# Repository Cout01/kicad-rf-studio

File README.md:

# kicad-rf-studio

kicad-rf-studio imports KiCad boards and simulates their RF parts with openEMS. It is free software, licensed under the GNU General Public License v3.0 or later (see `LICENSE`); its copy of CSXCAD's SmoothMeshLines is under the GNU Lesser General Public License v3.0 or later (see `COPYING.LESSER`).

*Em português: [README.pt-BR.md](README.pt-BR.md).*

## Install

kicad-rf-studio runs from a virtual environment of its own, `<venv>` below. pip installs it there with its Python dependencies, Qt among them (about 600 MB on disk); openEMS 0.37 comes apart. Until kicad-rf-studio is on PyPI, `<source>` is the source zip of a release on the project's GitHub page, once the project is published there, or a clone of this repository.

### Windows

In PowerShell, on Windows 10 or 11:

1. Install Python 3.14, 64-bit, for your user: with the Python install manager (`py install 3.14`), which needs no admin rights, or from python.org. The openEMS 0.37 wheels for Windows need Python 3.13 or 3.14.
2. Make the venv at `%LOCALAPPDATA%\kicad-rf-studio\venv` and install kicad-rf-studio into it. `$venv` names it in the commands below; a new PowerShell window needs that first line again.

   ```
   $venv = "$env:LOCALAPPDATA\kicad-rf-studio\venv"
   py -3.14 -m venv $venv
   & "$venv\Scripts\python" -m pip install <source>
   ```

3. Unpack the official Windows package of openEMS 0.37 and give its folder, the one that holds `openEMS.exe` and `python\`, to `setup-openems`. It installs the package's openEMS and CSXCAD wheels into the venv, offline, and records the folder.

   ```
   & "$venv\Scripts\kicad-rf-studio" setup-openems "<openEMS folder>"
   ```

4. Start KiCad once first, so that it makes its version's folder (or name the version with `--kicad 9.0` or `--kicad 10.0`). Install the KiCad button, for KiCad 9.0.7 or later, or 10.x. It writes into each KiCad version's plugins folder and never edits KiCad's settings. Then, in KiCad: Preferences › Plugins › Enable KiCad API, then restart KiCad.

   ```
   & "$venv\Scripts\kicad-rf-studio" install-kicad-plugin
   ```

5. Start the GUI with `& "$venv\Scripts\kicad-rf-studio-gui"`, or from KiCad's PCB editor: select the chain's two end pads, the antenna footprint (or one of its pads) and the radio pin, or a track, arc or via of a signal-integrity line, and press the kicad-rf-studio button. After updating kicad-rf-studio, run `install-kicad-plugin` again: the button's tooltip, which says what it takes, is written there.

### Linux

On Debian 12, Ubuntu 24.04 or Fedora (glibc 2.34 or newer), with the system Python (3.11 or newer):

1. Clone upstream's openEMS-Project at v0.37.0, with its submodules, and install its build dependencies. This is the one step that needs admin rights: the script asks, then installs your distribution's packages with sudo, `python3-venv` among them on Debian and Ubuntu.

   ```
   git clone --recursive --branch v0.37.0 https://github.com/thliebig/openEMS-Project.git
   cd openEMS-Project
   ./scripts/install_deps.sh --install --python
   ```

2. Make the venv at `~/.local/share/kicad-rf-studio/venv`, activate it and install kicad-rf-studio into it:

   ```
   python3 -m venv ~/.local/share/kicad-rf-studio/venv
   source ~/.local/share/kicad-rf-studio/venv/bin/activate
   pip install <source>
   ```

3. With the venv active, build openEMS in the openEMS-Project folder, without sudo, so that its Python bindings land in the venv: `./update_openEMS.sh ~/.local/share/kicad-rf-studio/openEMS --python`. Leave the GUI build on (no `--disable-GUI`): it builds AppCSXCAD.
4. Start KiCad once first, so that it makes its version's folder (or name the version with `--kicad 9.0` or `--kicad 10.0`). With the venv active, install the KiCad button: `kicad-rf-studio install-kicad-plugin`. Then, in KiCad: Preferences › Plugins › Enable KiCad API, then restart KiCad. A Flatpak KiCad cannot start the button: open the board in the GUI instead.
5. Start the GUI with `kicad-rf-studio-gui`. On a desktop, Qt needs the xcb cursor library: `libxcb-cursor0` on Debian and Ubuntu, `xcb-util-cursor` on Fedora.

### After installing

- **Moved the venv?** Its `kicad-rf-studio` programs and the button's launcher still name its old place. Reinstall kicad-rf-studio, then run `install-kicad-plugin` again, both through the Python of the venv where it now is: `& "<venv>\Scripts\python" -m pip install --force-reinstall --no-deps <source>`, then `& "<venv>\Scripts\python" -m kicad_rf_studio install-kicad-plugin` (Linux: `<venv>/bin/python` in both). Until then the button fails: KiCad 10 shows the shell's error, KiCad 9 nothing.
- **Remove the button:** `& "$venv\Scripts\kicad-rf-studio" install-kicad-plugin --remove` (Linux, with the venv active: `kicad-rf-studio install-kicad-plugin --remove`) deletes its folder from each KiCad version's plugins folder, and nothing else. Once the venv is gone, delete the `kicad-rf-studio` folder by hand from each `Documents\KiCad\<version>\plugins` (Windows) or `~/.local/share/kicad/<version>/plugins` (Linux).
- **Uninstall:** remove the button, then delete the venv; on Linux, also the openEMS folder `~/.local/share/kicad-rf-studio/openEMS` and the openEMS-Project clone. The folder that holds the venv, `%LOCALAPPDATA%\kicad-rf-studio` or `~/.local/share/kicad-rf-studio`, also holds the settings and the run folders your projects' results point to: delete it only when no project needs them.
- **English on a Portuguese Windows:** kicad-rf-studio speaks the language that `LANGUAGE`, `LC_ALL`, `LC_MESSAGES` or `LANG` names when one is set, else Brazilian Portuguese when Windows' display language is Portuguese (Brazil), else English. To keep English, run `setx LANGUAGE en` once and restart KiCad; git and other programs that read `LANGUAGE` turn English too. On Linux, put `export LANGUAGE=en` in your profile.

## Tutorial

This takes `lpf915`, the synthetic 915 MHz low-pass filter in `tests/fixtures` (a series DC block and a C-L-C pi of 0402 parts on a 50 Ω GCPW, under a shield), through `new`, `cost`, `run`, `retune` and `verify`. Run the commands from the root of a clone, or of the unpacked source zip, with the venv from Install. In PowerShell, `<venv>\Scripts\kicad-rf-studio` is `& "$venv\Scripts\kicad-rf-studio"`; on Linux, with the venv active, type `kicad-rf-studio` alone.

The times were measured on the development PC (Windows 11, 16 CPUs, 4 jobs at once) at the Normal preset, `new`'s default: by P0-B (`docs/validation/2026-10-25-p0-b.md`), unless marked as measured while this tutorial was written. P0-B's run B6 is this project: lpf915 at the protected reach of 6 substrate heights that `new` now writes. The excerpts are real output, from P0-B's runs or from runs made while this tutorial was written; `<run folder>` stands for the run's folder in the per-user data folder, and `lpf915` for the project's folder.

**`new`** reads the board, traces the chain between the pads U1.1 and J1.1 and writes the project. `--lid-height` is the height of the shield's lid in mm.

```
<venv>\Scripts\kicad-rf-studio new tests/fixtures/lpf915.kicad_pcb --start U1.1 --end J1.1 --f0 915MHz --lid-height 2.5 -o lpf915
```

It prints the stackup, the chain, each part and port, and every default it wrote:

```
Chain U1.1 → J1.1: series C1, L1, R1; shunt C2, C3, R2.
Port P1: signal U1.1, reference U1.2 (ic).
Port P2: signal J1.1, reference J1.2 (connector).
Preset normal (provisional default), band factor 1.1, T_max 40 ns, harmonics 3, mesh n 2, region 3 substrate heights past the chain, margin scale 1, protected reach 6 substrate heights.
Wrote lpf915\project.json.
```

**`cost`** prints the 2D Z0 and εeff of the chain's straight sections, then runs openEMS's setup-only gate and prints what a run will cost. On a machine with no calibration yet, it first measures the machine's speed, once. Measured while this tutorial was written, it took 40 s.

```
<venv>\Scripts\kicad-rf-studio cost lpf915
```

```
RF_B on F.Cu: width 0.600 mm, gap 0.150, length 2.035 mm — Z0 49.89 Ω, εeff 2.655 without mask; Z0 47.04 Ω, εeff 2.985 with mask
Cells: 332 × 195 × 69 = 4.47 M (mesh n 2, cell d 0.0751 mm).
Worst case: 13 h 16 min for 6 runs to T_max 40 ns, 4 at once with 4 threads each.
RAM: about 3.2 GB (4 jobs at once).
Main cost: 6 runs, one per port, 4 of them part ports.
```

Plan 6's mesh rule (spec §5.4, A-8) moved lpf915's lines after P0-B; the run times below are P0-B's.

That worst case comes from today's calibration, which each run refreshes. P0-B's B6 recorded a worst case of 46937 s (13.0 h) and, from its run's stop times, a prediction of 35801 s (9.9 h); after a `run`, `cost` prints that prediction too.

**`run`** runs the gates, then one job per port (P1 and P2, and the part ports C1, L1, C2 and C3) under the stop rule. When every job keeps S, it records the results in `project.json` and writes `layout.s6p`, `chain.s2p`, `summary.csv` and `summary.png` to `lpf915\results`. B6's six jobs took 19714 s (5.5 h), 0.55 of that prediction, and all six converged:

```
<venv>\Scripts\kicad-rf-studio run lpf915
```

```
Running 6 jobs, 4 at once, in <run folder>. Create a file named STOP there, or press Ctrl+C, to stop.
P1: converged at 13.79 ns (residual -67.2 dB).
P2: converged at 30.47 ns (residual -69.4 dB).
C1: converged at 13.95 ns (residual -66.7 dB).
L1: converged at 18.67 ns (residual -69.2 dB).
C2: converged at 13.83 ns (residual -70.0 dB).
C3: converged at 22.77 ns (residual -67.9 dB).
6 of 6 jobs kept S, in 5 h 28 min; results recorded in lpf915\project.json.
f0 = 915 MHz (|a| -8.1 dB): IL 2.54 dB and RL 3.70 dB with layout; IL 1.96 dB and RL 4.52 dB ideal schematic.
```

**`retune`** stores new part values and writes `lpf915\results` again from the last run's waves, with no new run. Measured while this tutorial was written, it took 2.3 to 2.4 s in four runs on a copy of B6:

```
<venv>\Scripts\kicad-rf-studio retune lpf915 C2=4.7pF
```

```
f0 = 915 MHz (|a| -8.1 dB): IL 3.91 dB and RL 2.40 dB with layout; IL 3.05 dB and RL 3.09 dB ideal schematic.
Relative / what-if: the instant retune is not yet validated against a full simulation of a real board (spec 7.6), so read these chain results as relative. Check the final values with `kicad-rf-studio verify lpf915\project.json`.
```

The retune stays labelled relative / what-if until P0-C passes: `run` and `retune` print that line, and `chain.s2p` and `summary.png` carry it. P0-B failed, so P0-C is recorded "do not start" and the label stays on.

**`verify`** runs once more with each part in the grid at its ideal value, only P1 and P2 as jobs, and compares that with a retune at the same values. It was not timed at reach 6. P0-B's B2, `verify` on lpf915 at the reach then in force (3 substrate heights), took 7077 s (2.0 h). Its P1 job converged and its P2 job reached T_max:

```
<venv>\Scripts\kicad-rf-studio verify lpf915
```

```
P1: converged at 30.18 ns (residual -71.4 dB).
P2: not converged where its S ends, at 39.99 ns with a residual of -69.7 dB: at T_max, or, for a signal-integrity job whose residual still fell fast enough there, past it, where that fall slowed or the ring rule's ceiling came. S is kept and flagged; raise t_max_s in project.json for a converged result.
```

P0-B's consistency criterion, `verify` against the co-simulation, failed (|ΔS21| at f0 0.1019 dB against 0.1 dB, max |ΔS| 0.0926 against 0.03), and P0-B was decided fail at the ceiling. Read P0-B's report before you take `verify`'s comparison as agreement.

## Antenna tutorial

This takes `ifa2g4_pi`, the synthetic 2.4 GHz board in `tests/fixtures` (KiCad's `Texas_SWRA117D_2.4GHz_Left` inverted-F, after TI's application note SWRA117D, fed from the radio's pad U1.1 through a pi network of 0402 parts: series L1, shunts C2 and C3), through `new --antenna`, `cost`, `run`, `retune` and `verify`, then compares it with `ifa2g4_pi_pour`, the same board with a ground pour inside the antenna's clearance. Run the commands as in the Tutorial above.

The times were measured on the development PC (Windows 11, 16 CPUs) at the Normal preset, `new`'s default, by the run through the GUI that closed Stage 3 (`docs/validation/2026-11-02-stage3-exit.md`); that run compared with the pour that gate P3-E had verified, so the pour's run and verify times are P3-E's (`docs/validation/2026-11-01-p3-e.md`). `cost` prints your own machine's estimate before every run, and no runtime is promised. The excerpts are real output of that run; `ifa2g4_pi`, `ifa2g4_pi_pour` and `compare` stand for the projects' and the compare's folders.

**`new --antenna`** finds the antenna footprint AE1 and its feed pad, traces the chain from the radio's pin U1.1 to it, and writes an antenna project for the band: `--antenna` takes the place of `--end` and `--band F_LO:F_HI` that of `--f0`. The whole board is simulated, in an air box with a PML absorber, and every part on the chain is a part port, so the network can be retuned.

```
<venv>\Scripts\kicad-rf-studio new tests/fixtures/ifa2g4_pi.kicad_pcb --start U1.1 --antenna AE1 --band 2400MHz:2483.5MHz -o ifa2g4_pi
```

It took under a second. It prints the stackup, the nets, the antenna and its join, the chain, each part and port, the band and every default it wrote:

```
Antenna AE1, fed at pad AE1.1 on net RF: its copper drawn without a net takes that net.
Antenna AE1 joins its feed to ground through AE1.2 by design, as an inverted-F does; the connectivity and port checks accept that join and no other.
Chain U1.1 → AE1.1: series L1; shunt C2, C3.
Port P1: signal U1.1, reference U1.2 (ic).
Band 2400 to 2483.5 MHz, f0 2441.75 MHz; the pulse spans 1840 to 2990 MHz.
Preset normal, T_max 30 ns (2·t0 + 60/f0), mesh n 2, measured region 6 substrate heights past the antenna and the chain, protected reach 6 substrate heights, air gap 31.2 mm (λ/4 at f_lo) to a pml_8 absorber, far-field frequencies: 11, on a 5° sphere.
Wrote ifa2g4_pi\project.json.
```

**`cost`** splits the cells into board, air and PML, and prints the worst case before any run.

```
<venv>\Scripts\kicad-rf-studio cost ifa2g4_pi
```

It took 37 s, 26 s of it measuring the machine's speed, which `cost` does once on a machine with no calibration yet:

```
Cells: 135 × 143 × 71 = 1.37 M (mesh n 2, cell d 0.3000 mm).
Cells: 0.11 M in the board, 0.67 M of air and 0.60 M of PML; the time counts a PML cell as 8.92 cells and runs this model at 0.559 × the calibrated speed for that many jobs at once (gate P3-A's method, refitted by gates P3-B to P3-E).
dt 1.2625e-13 s (floor 0.8 × 1.1118e-13 s), set by the z edge at (98.642, 93.865, 0.000) mm.
Worst case: 3 h 48 min for 4 runs to T_max 30 ns, 2 at once with 8 threads each.
RAM: about 0.6 GB (2 jobs at once).
```

**`run`** runs one job per port, P1 at the radio's pin and the part ports L1, C2 and C3, as many at once as the machine's calibration chose (two here). It gives S11 at the radio's pin for any part values, and no far field: a part port is not a part.

```
<venv>\Scripts\kicad-rf-studio run ifa2g4_pi
```

It took 3833 s (1.1 h), 0.28 of that worst case, and all four jobs converged. These results are at the board's own values, L1 2.7nH and C2 and C3 1pF:

```
P1: converged at 11.12 ns (residual -60.2 dB).
L1: converged at 11.95 ns (residual -60.7 dB).
C2: converged at 11.12 ns (residual -60.4 dB).
C3: converged at 12.58 ns (residual -60.6 dB).
4 of 4 jobs kept S, in 1 h 3 min; results recorded in ifa2g4_pi\project.json.
Resonance (lowest |S11|): 2325.8 MHz, |S11| -6.9 dB, Zin at U1.1 43.2 - j46.7 Ω.
f_lo = 2400.0 MHz: |S11| -5.6 dB, Zin at U1.1 17.5 - j16.0 Ω, mismatch efficiency 72.6 %.
f0 = 2441.8 MHz: |S11| -4.7 dB, Zin at U1.1 13.3 - j4.2 Ω, mismatch efficiency 66.2 %.
f_hi = 2483.5 MHz: |S11| -4.0 dB, Zin at U1.1 11.5 + j5.9 Ω, mismatch efficiency 60.2 %.
-10 dB bandwidth: none, as |S11| stays above -10 dB.
-6 dB bandwidth: 2274.2 to 2384.3 MHz (110.1 MHz).
No far field for this run: a run with part ports records none, as its jobs hold ports where the matching parts sit; `kicad-rf-studio verify ifa2g4_pi\project.json` runs one job with each part in the grid at its value, as an ideal part, and records it.
```

**`retune`** closes the part ports at new values, with no new run. These came from an E24 search over the run's layout, the values the GUI's snapping gives (C2 typed as 0.127pF snaps to 0.13pF). `0R` replaces a series part with a short and `open` removes a shunt part: `retune ifa2g4_pi L1=0R C2=open C3=open` shows the antenna through its feed line.

```
<venv>\Scripts\kicad-rf-studio retune ifa2g4_pi L1=0R C2=0.13pF C3=1pF
```

It took 2 s:

```
Resonance (lowest |S11|): 2443.4 MHz, |S11| -17.4 dB, Zin at U1.1 60.6 - j10.5 Ω.
f_lo = 2400.0 MHz: |S11| -10.3 dB, Zin at U1.1 65.8 + j33.1 Ω, mismatch efficiency 90.7 %.
f0 = 2441.8 MHz: |S11| -17.4 dB, Zin at U1.1 62.1 - j9.2 Ω, mismatch efficiency 98.2 %.
f_hi = 2483.5 MHz: |S11| -10.5 dB, Zin at U1.1 32.1 - j17.6 Ω, mismatch efficiency 91.1 %.
-10 dB bandwidth: 2397.7 to 2486.6 MHz (89.0 MHz).
-6 dB bandwidth: 2356.6 to 2521.5 MHz (164.9 MHz).
Relative / what-if: the instant retune is not yet validated against a full simulation of a real board (spec 7.6), so read these chain results as relative. Check the final values with `kicad-rf-studio verify ifa2g4_pi\project.json`.
```

**`verify`** runs one job with every part in the grid at its applied value, as an ideal part, and records the far field: the radiation and total efficiency, the directivity, gain and realized gain, and the three cuts at f0 in `verify_summary.png`. After it, `retune` also prints the what-if total efficiency of each new set of values.

```
<venv>\Scripts\kicad-rf-studio verify ifa2g4_pi
```

It took 1161 s (19 min). It prints a far-field line for each of the eleven far-field frequencies; this excerpt keeps f0's:

```
1 verify jobs kept S, in 19 min; the comparison is stored in ifa2g4_pi\project.json.
Resonance (lowest |S11|): 2446.6 MHz, |S11| -12.5 dB, Zin at U1.1 74.7 - j16.5 Ω.
f_lo = 2400.0 MHz: |S11| -9.3 dB, Zin at U1.1 71.6 + j37.8 Ω, mismatch efficiency 88.3 %.
f0 = 2441.8 MHz: |S11| -12.5 dB, Zin at U1.1 78.3 - j11.6 Ω, mismatch efficiency 94.4 %.
f_hi = 2483.5 MHz: |S11| -10.1 dB, Zin at U1.1 43.0 - j29.7 Ω, mismatch efficiency 90.2 %.
verify against the retune at the same ideal values: |ΔS11| 0.0076 at f0 = 2441.75 MHz (|a| -0.1 dB) and 0.0149 at most up to f2.
Resonance at 2446.6 MHz in verify against 2446.8 MHz in the retune: a shift of -0.01 %.
2441.8 MHz: radiation efficiency 81.3 %, total efficiency 76.7 %, directivity 2.55 dBi, gain 1.65 dBi, realized gain 1.40 dBi.
verify checks the layout reduction, not the vendor part data: each part sat in the grid at its value as an ideal part, without the package ESL, ESR and Cp or the S2P data the retune applies, a 0 Ω part as copper and an open part left out, against a retune at the same ideal values; its far field holds that ideal network.
```

**`compare`** reads both projects' verified results, which must share every setting, and marks each difference resolved or not. First the same steps on the pour board, then the compare, which writes `compare.csv` and `compare.png` into `compare`:

```
<venv>\Scripts\kicad-rf-studio new tests/fixtures/ifa2g4_pi_pour.kicad_pcb --start U1.1 --antenna AE1 --band 2400MHz:2483.5MHz -o ifa2g4_pi_pour
<venv>\Scripts\kicad-rf-studio run ifa2g4_pi_pour
<venv>\Scripts\kicad-rf-studio retune ifa2g4_pi_pour L1=0R C2=0.13pF C3=1pF
<venv>\Scripts\kicad-rf-studio verify ifa2g4_pi_pour
<venv>\Scripts\kicad-rf-studio compare ifa2g4_pi ifa2g4_pi_pour -o compare
```

On the pour, `new` and `retune` take seconds, and `run` and `verify` took 1 h 4 min and 27 min in gate P3-E (`docs/validation/2026-11-01-p3-e.md`). The compare took 1 s:

```
Resonance: 2446.6 MHz to 2358.2 MHz, a shift of -88.5 MHz (-3.62 % of f0): resolved.
-10 dB bandwidth: not compared, as one of the two has none bounded inside the simulated band.
Total efficiency at f_lo = 2400.0 MHz: 71.8 % to 56.1 %, -1.07 dB: resolved.
Total efficiency at f0 = 2441.8 MHz: 76.7 % to 48.4 %, -2.00 dB: resolved.
Total efficiency at f_hi = 2483.5 MHz: 73.0 % to 39.0 %, -2.73 dB: resolved.
Peak gain at f0 = 2441.8 MHz: 1.65 dBi to 1.21 dBi, -0.44 dB: resolved.
Resolved means larger than the significance threshold: 0.3 % of f0 for a frequency and 0.2 dB for an efficiency or a gain, set by gate P3-D at three times the model's measured noise floor and never below 0.3 % and 0.2 dB.
Wrote compare.csv, compare.png in compare.
```

In the GUI, New's kind Antenna takes the antenna footprint, the start pad and a band preset; Results shows S11 with the band shaded, the Smith chart and, from the run that holds the network, the efficiencies and the three cuts, its title naming that run; the Compare tab compares the open project with a variant. The KiCad button pre-fills New with the antenna kind when the antenna footprint, or one of its pads, is selected with the radio's pin.

### What these results do not tell you

- Every antenna result carries this line: "Relative: these antenna results compare variants of one board under identical settings; they do not predict measured performance."
- The board is alone in free space: no enclosure, hand, battery or cable. TI's AN043 measured a 5–10 MHz shift from a cable's position alone.
- Copper is a perfect conductor, so the radiation efficiency reads high; the parts' bodies are absent, and the parts off the chain are approximated.
- A difference is resolved only above 0.3 % of f0 for a frequency and 0.2 dB for an efficiency or a gain, at least three times the model's measured noise floor (gate P3-D, `docs/validation/2026-11-01-p3-d.md`). This antenna's resonance moves about 1.9 % per mm of its position near the ground's corner, which compare resolves.
- The retune stays what-if until P0-C: `verify` checks the layout reduction with ideal parts, not the vendor parts, and here its ideal network reads −12.5 dB at f0 where the retune's 0402 presets read −17.4 dB.
- Chip antennas and modules are refused, the matching chain up to their pad still runs as in the Tutorial, and sheet copper is not offered.
- A radio pin, feed and antenna pad in one line can be refused by the fit2d gate; raising `gates.fit2d_limit` in project.json is at your own risk.
- `meander915` is no 915 MHz example: on its synthetic board it resonates above its band.

## Signal-integrity tutorial

This takes `usb2_hs`, the synthetic four-layer USB 2.0 high-speed board in `tests/fixtures`: a micro-B connector J1, the pads of a six-pin ESD array U2 on the pair, a 22 Ω 0402 series resistor on each leg (R1 and R2) and an MCU-like QFN U1 at the far end, with a neighbour net, AUX, running beside part of the route between the test points TP1 and TP2. It goes through `new --interface`, `cost`, `run`, `retune` and `verify`, then compares it with `usb2_hs_gap`, the same board with a slot in the plane under the pair. Run the commands as in the Tutorial above.

The times were measured on the development PC (Windows 11, 16 CPUs) at the Normal preset, `new`'s default, by the run through the GUI that closed Stage 4 (`docs/validation/2026-11-09-stage4-exit.md`). That run compared with the plane-gap board that gate P4-F had run (`docs/validation/2026-11-08-p4-f.md`), retuned and verified for it, so the gap's run time is P4-F's and its verify time that preparation's. `cost` prints your own machine's estimate before every run, and no runtime is promised. The excerpts are real output of that run; `<run folder>` stands for a run's folder in the per-user data folder, and `usb2_hs`, `usb2_hs_gap` and `compare` for the projects' and the compare's folders.

**`new --interface`** traces the measured line from the connector's pin J1.3 through R1 to the MCU's pin U1.3, takes its partner by KiCad's pair rule (`--pair`: USB_D+ with USB_D-, ending at J1.2 and U1.2) and AUX between TP1.1 and TP2.1 as a victim, and writes a signal-integrity project for the `usb2-hs` interface: 90 Ω differential ± 10 %, the link's 500 ps edge and a 240 MHz marker, simulated to 10 GHz. R1 and R2 are part ports, so their values can be retuned.

```
<venv>\Scripts\kicad-rf-studio new tests/fixtures/usb2_hs.kicad_pcb --start J1.3 --end U1.3 --interface usb2-hs --pair --victim TP1.1:TP2.1 -o usb2_hs
```

It took 10 s. It prints the stackup, the nets, the interface, the pair, both chains, the victim, each part and port and every default it wrote; this excerpt leaves out the part lines:

```
Stackup: board, dielectric 1.44 mm, εr 4.3; mask 0.01 mm, εr 3.3.
GND nets: GND. Power nets: +3V3, VBUS. Connectors: J1. Shields: none.
Interface usb2-hs: target 90 Ω differential ± 10 %, the link's rise time 500 ps, marker 240 MHz, simulated to 10 GHz, where the localising TDR's rise time is 125 ps.
Pair: USB_D+ with USB_D-, by KiCad's pair rule.
Chain J1.3 → U1.3: series R1; shunt none.
Chain J1.2 → U1.2: series R2; shunt none.
Victim TP1.1 → TP2.1 on net AUX: its two ends are ports, so the waves coupled into it end in 50 Ω.
Port P1: signal J1.3, vertical to the plane on In1.Cu.
Port P2: signal J1.2, vertical to the plane on In1.Cu.
Port P3: signal U1.3, reference U1.17 (ic).
Port P4: signal U1.2, reference U1.17 (ic).
Port P5: signal TP1.1, vertical to the plane on In1.Cu.
Port P6: signal TP2.1, vertical to the plane on In1.Cu.
Preset normal (provisional default), T_max 9 ns, stop window 2 ns, mesh n 2 with the cell d throughout the protected extent (gate P4-C), dielectric lossless, timestep floor 0.6, region and protected reach 6 substrate heights (1.2 mm).
Wrote usb2_hs\project.json.
```

**`cost`** first lists the 2D table, every straight section's impedance against the target band, in seconds and before any run; then the cells, the runs broken down into the lines' ends, the victim's and the part ports, the worst case, and the time a job whose planes ring may take past T_max.

```
<venv>\Scripts\kicad-rf-studio cost usb2_hs
```

It took 72 s, including the measurement of the machine's speed that `cost` makes once on a machine with no calibration yet:

```
2D table against the target 90 Ω ± 10 % (a pair's Zdiff, a net's Z0), mask included; bends, vias, pads and parts not included: a screening before the run, not its result.
USB_D+ on F.Cu, coupled: width 0.300 mm, gap 0.253 mm, length 2.038 mm — Zdiff 90.87 Ω (Zodd 45.44 Ω, Zeven 59.18 Ω), εeff odd 3.054, even 3.493, delay 11.9 ps: in the target band.
USB_D+ on F.Cu: width 0.300 mm, length 0.675 mm, its partner not alongside — Z0 52.51 Ω, so Zdiff 105.01 Ω uncoupled, εeff 3.312, delay 4.1 ps: outside the target band.
USB_D+ on F.Cu, coupled: width 0.600 mm, gap 1.300 mm, length 5.000 mm — Zdiff 70.25 Ω (Zodd 35.12 Ω, Zeven 35.73 Ω), εeff odd 3.419, even 3.496, delay 30.8 ps: outside the target band.
USB_D+ on F.Cu: width 0.300 mm, length 0.675 mm, its partner not alongside — Z0 52.59 Ω, so Zdiff 105.18 Ω uncoupled, εeff 3.311, delay 4.1 ps: outside the target band.
USB_D+ on F.Cu, coupled: width 0.300 mm, gap 0.250 mm, length 17.490 mm — Zdiff 90.21 Ω (Zodd 45.10 Ω, Zeven 58.90 Ω), εeff odd 3.061, even 3.493, delay 102.1 ps: in the target band.
MCU_D+ on F.Cu, coupled: width 0.300 mm, gap 0.250 mm, length 4.527 mm — Zdiff 90.34 Ω (Zodd 45.17 Ω, Zeven 59.03 Ω), εeff odd 3.061, even 3.500, delay 26.4 ps: in the target band.
USB_D- on F.Cu, coupled: width 0.300 mm, gap 0.251 mm, length 2.038 mm — Zdiff 90.32 Ω (Zodd 45.16 Ω, Zeven 58.96 Ω), εeff odd 3.063, even 3.501, delay 11.9 ps: in the target band.
USB_D- on F.Cu: width 0.300 mm, length 0.675 mm, its partner not alongside — Z0 52.51 Ω, so Zdiff 105.01 Ω uncoupled, εeff 3.312, delay 4.1 ps: outside the target band.
USB_D- on F.Cu, coupled: width 0.600 mm, gap 1.300 mm, length 5.000 mm — Zdiff 70.25 Ω (Zodd 35.12 Ω, Zeven 35.73 Ω), εeff odd 3.419, even 3.496, delay 30.8 ps: outside the target band.
USB_D- on F.Cu: width 0.300 mm, length 0.675 mm, its partner not alongside — Z0 52.59 Ω, so Zdiff 105.18 Ω uncoupled, εeff 3.311, delay 4.1 ps: outside the target band.
USB_D- on F.Cu, coupled: width 0.300 mm, gap 0.250 mm, length 17.490 mm — Zdiff 90.21 Ω (Zodd 45.10 Ω, Zeven 58.90 Ω), εeff odd 3.061, even 3.493, delay 102.1 ps: in the target band.
MCU_D- on F.Cu, coupled: width 0.300 mm, gap 0.250 mm, length 4.527 mm — Zdiff 90.24 Ω (Zodd 45.12 Ω, Zeven 58.99 Ω), εeff odd 3.063, even 3.502, delay 26.4 ps: in the target band.
AUX on F.Cu: width 0.200 mm, gap 0.625, length 12.000 mm — Z0 62.94 Ω, εeff 3.240, delay 72.0 ps: a victim, no target.
Cells: 402 × 121 × 77 = 3.75 M (mesh n 2, cell d 0.1000 mm).
dt 8.0779e-14 s (floor 0.6 × 7.4439e-14 s), set by the z edge at (96.588, 100.925, 1.580) mm.
Worst case: 1 h 51 min for 8 runs to T_max 9 ns, 4 at once with 4 threads each.
Runs: 4 for the measured lines' ends, 2 for the victims' ends, 2 for the part ports.
A job whose port residual still falls by 0.3 dB/ns or more at T_max, fast enough over its last 3 ns to reach the preset's level by 36 ns, runs on while it keeps doing so, until it converges: up to 7 h 24 min.
RAM: about 2.7 GB (4 jobs at once).
Main cost: 8 runs, one per port, 2 of them part ports.
```

**`run`** runs one job per port: the pair's four ends, the victim's two and the part ports R1 and R2. It gives the TDR along the route against the target band, the mixed-mode S (Sdd21, Sdd11, Scc21 and Scd21), the skew and the crosstalk into AUX, for any values of R1 and R2.

```
<venv>\Scripts\kicad-rf-studio run usb2_hs
```

It took 2351 s (39 min), 0.35 of that worst case, and all eight jobs converged. These results are at the board's own values, 22 Ω on R1 and R2:

```
P1: converged at 3.06 ns (residual -60.9 dB).
P2: converged at 3.06 ns (residual -60.7 dB).
P3: converged at 3.04 ns (residual -62.5 dB).
P4: converged at 3.04 ns (residual -62.4 dB).
P5: converged at 2.74 ns (residual -60.4 dB).
P6: converged at 2.76 ns (residual -62.1 dB).
R1: converged at 2.99 ns (residual -61.4 dB).
R2: converged at 2.99 ns (residual -61.2 dB).
8 of 8 jobs kept S, in 38 min; results recorded in usb2_hs\project.json.
Results of the run in <run folder> at preset normal: 8 jobs converged, 0 flat, 0 at T_max.
Passivity: σ_max 1.0083 at worst, at 10000.0 MHz (|a| -19.6 dB); flagged above 1.02.
Reciprocity: |Sij − Sji| 1.53e-02 at worst, at 10000.0 MHz (|a| -19.6 dB); flagged above 0.02.
Relative: these signal-integrity results compare variants of one board under identical settings; they do not predict measured performance.
Sdd21 -1.912 dB at the marker (240 MHz) and -2.900 dB at f_max (10 GHz).
The worst Sdd11 up to f_max: -7.43 dB at 4815 MHz.
The worst Scd21 up to f_max: -45.56 dB at 10000 MHz.
Scc21, the common mode's transmission: -1.90 dB at the marker (240 MHz).
The differential TDR: the localising rise time 125 ps resolves 10.3 mm and the link's 500 ps 41.4 mm, at the route's 2D εeff 3.28; the first resolution length at each port is the port's own launch.
The lowest TDR level between the launches, 84.97 Ω at 131.2 ps (10.9 mm), lies on a feature shorter than two resolution lengths (20.7 mm), so it is not that feature's impedance.
The highest TDR level between the launches, 96.10 Ω at 256.2 ps (21.2 mm), lies on a feature shorter than two resolution lengths (20.7 mm), so it is not that feature's impedance.
Intra-pair skew -0.01 ps: the N leg's TDT arrives at 199.9 ps and the P leg's at 199.9 ps, each at half its peak.
Crosstalk into AUX from the pair driven differentially at its start: NEXT at TP1.1 peaks at -25.72 dB (9170 MHz) and FEXT at TP2.1 at -28.92 dB (9360 MHz).
Not in S: the copper's loss over the route's 30.4 mm, by Hammerstad's formula for smooth copper, about 0.050 dB at the marker (240 MHz) and 0.321 dB at f_max (10 GHz).
Not in S either, the dielectric being lossless: its loss over the same length, about 0.022 dB at the marker and 0.907 dB at f_max.
```

**`retune`** closes the part ports at new values, with no new run: 24 Ω, the value the GUI's E24 snapping gives a typed 25 Ω. `0R` replaces a series part with a short.

```
<venv>\Scripts\kicad-rf-studio retune usb2_hs R1=24 R2=24
```

It took 7 s:

```
Relative: these signal-integrity results compare variants of one board under identical settings; they do not predict measured performance.
Sdd21 -2.067 dB at the marker (240 MHz) and -3.092 dB at f_max (10 GHz).
The worst Sdd11 up to f_max: -7.20 dB at 4805 MHz.
The worst Scd21 up to f_max: -45.70 dB at 10000 MHz.
Scc21, the common mode's transmission: -2.06 dB at the marker (240 MHz).
The differential TDR: the localising rise time 125 ps resolves 10.3 mm and the link's 500 ps 41.4 mm, at the route's 2D εeff 3.28; the first resolution length at each port is the port's own launch.
The lowest TDR level between the launches, 84.97 Ω at 131.2 ps (10.9 mm), lies on a feature shorter than two resolution lengths (20.7 mm), so it is not that feature's impedance.
The highest TDR level between the launches, 96.38 Ω at 256.2 ps (21.2 mm), lies on a feature shorter than two resolution lengths (20.7 mm), so it is not that feature's impedance.
Intra-pair skew -0.01 ps: the N leg's TDT arrives at 199.8 ps and the P leg's at 199.9 ps, each at half its peak.
Crosstalk into AUX from the pair driven differentially at its start: NEXT at TP1.1 peaks at -25.67 dB (9160 MHz) and FEXT at TP2.1 at -28.80 dB (9340 MHz).
Not in S: the copper's loss over the route's 30.4 mm, by Hammerstad's formula for smooth copper, about 0.050 dB at the marker (240 MHz) and 0.321 dB at f_max (10 GHz).
Not in S either, the dielectric being lossless: its loss over the same length, about 0.022 dB at the marker and 0.907 dB at f_max.
Relative / what-if: the instant retune is not yet validated against a full simulation of a real board (spec 7.6), so read these chain results as relative. Check the final values with `kicad-rf-studio verify usb2_hs\project.json`.
```

**`verify`** runs one job per external port with R1 and R2 in the grid at their values, as ideal parts, and compares the result with the retune's.

```
<venv>\Scripts\kicad-rf-studio verify usb2_hs
```

It took 1815 s (30 min), and all six jobs converged. This excerpt keeps the comparison with the retune:

```
6 verify jobs kept S, in 29 min; the comparison is stored in usb2_hs\project.json.
verify against the retune at the same ideal values: max |ΔS| 0.0292 from the first point above DC to f_max, at 9920 MHz (|a| -19.2 dB).
The lowest TDR level between the launches, verify against the retune: 84.97 Ω against 84.97 Ω; one of them lies on a feature shorter than two resolution lengths, so it is not that feature's impedance.
The highest TDR level between the launches, verify against the retune: 92.67 Ω against 93.06 Ω; one of them lies on a feature shorter than two resolution lengths, so it is not that feature's impedance.
verify checks the layout reduction, not the vendor part data: each part sat in the grid at its value as an ideal part, without the package ESL, ESR and Cp or the S2P data the retune applies, a 0 Ω part as copper and an open part left out, against a retune at the same ideal values, whose loads hold at DC their value at the grid's first point above DC.
```

**`compare`** reads both projects' verified results, which must share every setting, and marks each difference resolved or not. First the same steps on the plane-gap board, then the compare, which writes `compare.csv` and `compare.png` into `compare`:

```
<venv>\Scripts\kicad-rf-studio new tests/fixtures/usb2_hs_gap.kicad_pcb --start J1.3 --end U1.3 --interface usb2-hs --pair --victim TP1.1:TP2.1 -o usb2_hs_gap
<venv>\Scripts\kicad-rf-studio run usb2_hs_gap
<venv>\Scripts\kicad-rf-studio retune usb2_hs_gap R1=24 R2=24
<venv>\Scripts\kicad-rf-studio verify usb2_hs_gap
<venv>\Scripts\kicad-rf-studio compare usb2_hs usb2_hs_gap -o compare
```

On the plane-gap board, `new` and `retune` take seconds, `run` took 4 h 25 min in gate P4-F (`docs/validation/2026-11-08-p4-f.md`), and `verify` 3 h 35 min in the preparation for the run through the GUI. The compare took 9 s:

```
The lowest TDR level between the launches: 84.97 Ω against 85.31 Ω, +0.34 Ω: not resolved; one of them lies on a feature shorter than two resolution lengths, so it is not that feature's impedance, and the delta compares two levels filtered alike.
The highest TDR level between the launches: 92.67 Ω against 94.89 Ω, +2.22 Ω: resolved; one of them lies on a feature shorter than two resolution lengths, so it is not that feature's impedance, and the delta compares two levels filtered alike.
Sdd21 at 240 MHz: -2.068 dB against -2.067 dB, +0.001 dB: not resolved.
Sdd21 at 10000 MHz: -2.829 dB against -3.051 dB, -0.222 dB: resolved.
The worst Sdd11 up to f_max: -6.97 dB against -7.23 dB, -0.26 dB: not resolved.
The worst Scd21 up to f_max: -47.18 dB against -28.19 dB, +19.00 dB: resolved.
The intra-pair skew: -0.00 ps against +0.40 ps, +0.40 ps: not resolved.
NEXT into AUX, its peak: -25.87 dB against -20.98 dB, +4.89 dB: resolved.
FEXT into AUX, its peak: -29.42 dB against -23.58 dB, +5.84 dB: resolved.
Resolved means larger than the significance threshold: 2.2 Ω on a TDR level, 0.05 dB on Sdd21 or S21, 0.5 dB on Sdd11, S11, NEXT and FEXT where the higher of the two levels stands above -50 dB and on Scd21 where it stands above -37.7 dB, and 1 ps on the skew: the values gate P4-E set from the model's measured noise.
Wrote compare.csv, compare.png in compare.
```

In the GUI, New's kind Signal integrity takes the start and end pads, the interface, the pair (none, KiCad's rule or its two end pads picked) and up to two victims; the Cost tab lists the 2D table before the estimate; Results shows the TDR with the target band, the mixed-mode S and the crosstalk, and retunes R1 and R2 with E24 snapping; the Compare tab compares the open project with a variant. The KiCad button pre-fills New with the signal-integrity kind, the pair and an interface that fits it from a selected track, arc or via, and with the line's two end pads, the connector's first, when it has exactly two IC or connector pads: on `usb2_hs` the ESD array's pads make four, so pick J1.3 and U1.3, or select them in KiCad with a track of the pair.

### What these results do not tell you

- Every signal-integrity result carries this line: "Relative: these signal-integrity results compare variants of one board under identical settings; they do not predict measured performance."
- A TDR level marked short lies on a feature shorter than two resolution lengths, so it is not that feature's impedance; on this route about 1.1 resolution lengths lie between the launches, and the 2D table gives a straight section's impedance. A level within 2.2 Ω of a pair's target (1.1 Ω of a single net's) marks no feature, and the same values are compare's thresholds on a TDR level, three times the model's measured noise (gate P4-E, `docs/validation/2026-11-07-p4-e.md`).
- Copper staircased at 45° or along arcs is only warned about: gate P4-B measured a 45° pair 2.27 % (90 Ω) and 5.35 % (100 Ω) off its axis-aligned twin at mesh n 2, and whether such a pair is refused or run at a finer mesh is not decided yet (`docs/validation/2026-11-06-p4-b.md`).
- The dielectric is lossless by default, so S holds no dielectric loss, and the loss lines estimate it with the copper's. `"dielectric": "debye"` in project.json is the option, at a cost: a Debye cell weighs about 109 plain cells, so this board would run about 33 times slower (gate P4-D, `docs/validation/2026-11-07-p4-d.md`).
- A job whose port residual still falls fast enough at T_max runs on, up to four times T_max: the planes' cavity resonances ring in a lossless model, and they depend on the crop, so their frequencies and depths are no predictions. `cost` prints the time to that ceiling.
- `cost` prices a run of two jobs at once about 1.9 times too long, on the safe side, until a run with that many jobs at once measures the speed (`docs/validation/2026-11-08-p4-refit.md`).
- Copper is a perfect conductor; packages, dies and the connector's body are absent, and the ESD array is its pads alone; the ports are lumped at the pads.
- The retune stays what-if: `verify` checks the layout reduction with ideal parts, not the vendor parts.

## Review tutorial

This reviews `emc_review`, the synthetic four-layer board in `tests/fixtures` made for the review (50 × 50 mm, GND on In1.Cu and +3V3 on In2.Cu, with four clock nets and a shield, each a case of one rule), then `lpf915`, the Tutorial's filter. `review` reads the board as saved, measures its tagged nets and its shields against four geometry rules of thumb, R1 to R4, and solves the modes of its plane-pair cavities, in seconds and with no openEMS run. It writes `review.csv` (a row per finding), `review.json` (the settings, the findings with their KiCad IDs, and the cavities) and `review.png` (the outline, the planes' cover, the tagged tracks and each finding's number) into the folder that `-o` names, the working folder without it, and exits 0 with findings or without. Run the commands as in the Tutorial above.

The times were measured on the development PC while this tutorial was written. The excerpts are real output of these commands, run then with `-o` naming a temporary folder, which they show as `review`.

**`review`** on `emc_review`, with no option but the folder:

```
<venv>\Scripts\kicad-rf-studio review tests/fixtures/emc_review.kicad_pcb -o review
```

It took 2 s and printed:

```
Fills as saved — refill (B) in KiCad and save if you changed copper.
Geometry rules, not a compliance verdict: each finding measures the board as saved against a published rule of thumb, named with its source; nothing here predicts a pass or a fail.
Review at f_max 5 GHz (the default: FCC 15.33(b)(1)'s upper measurement frequency for a device whose highest frequency is 500 to 1000 MHz) and εr 4.5: λ/20 is 1.413 mm; the edge rule's k is 2.
Nets tagged by their names' patterns: CLK_EDGE, CLK_GAP, CLK_LOOK, CLK_MID.
#1 R1: CLK_GAP on F.Cu runs 6.000 mm over a void in its GND reference (In1.Cu, h 0.200 mm), 10.000 mm across, at (113.000, 110.000) mm; λ/20 at f_max is 1.413 mm. Crossing a split or void in the reference is a known return-path fault (LearnEMC; Ansys SIwave's Net Crossing Split; HyperLynx DRC); a run counts from 1 mm, a cut measured on three public boards.
#2 R3: CLK_EDGE on F.Cu runs 0.350 mm from the board edge at (113.000, 100.600) mm, under 2·h = 0.400 mm (h 0.200 mm to In1.Cu): about 16.5 % of its ideal return current would lie past the edge. Critical nets belong at least 2h from the board edge (LearnEMC).
Cavity 1: In1.Cu/In2.Cu, nets GND / +3V3, at (134.250, 121.650) mm: d 1.040 mm, εr 4.5, area 1697.5 mm², via posts 0.
Cavity 1's modes up to f_max, in MHz: 971.1, 1275.3, 1526.1, 2245.2, 2673.6, 2753.6, 2961.3, 3307.9, 3604.2, 4126.6, 4327.6, 4447.2, 4694.8, 4983.6.
Cavity 2: In1.Cu/In2.Cu, nets GND / GND, at (109.000, 125.000) mm: d 1.040 mm, εr 4.5, area 80.0 mm², via posts 1.
Cavity 2's modes up to f_max, in MHz: 1735.5, 3701.9.
Limits of the cavity modes: lossless, so the list says where a resonance may sit, never how high it rises; decoupling capacitors excluded; vias as posts only, snapped to the grid, and a post of drill 0.5 mm or more, a disc of held cells, puts the mode it makes up to about 6 % low; TM0 modes only; no fringing, so frequencies read high by about 2Δ/a, Δ about 0.4 to 0.5 d (about 0.3 % for d 0.2 mm on 50 mm, 2 % for 1 mm; gate E-E's openEMS run measured 1.0 % on a 50 × 30 mm pair at d 0.8 mm); εr uniform; the fills as saved; slots under 0.5 mm unresolved; cavities uncoupled across splits.
Findings: 2.
Wrote review.csv, review.json, review.png in review.
Limit: board-level keep-out areas leave no geometry in the import, so the review sees only the fills they shape; a footprint's keep-out, a connector or a printed antenna takes its copper out of R1 and R3.
```

**The tags.** R1 to R3 measure only tagged nets, and the review prints where its tags came from. With no `--net`, the name patterns tag a net whose name, after its last "/", matches one of seven families, CLK, SCK, XTAL, SW, SPI, I2S and USB, unless its last word, trailing digits stripped, is CTRL, NSS, DIO, BUSY, RST, IRQ, EN or CS: CLK_GEN is tagged, SPI_CS is not. Here they tagged the four clocks. `--net` names nets, or fnmatch patterns, in place of the patterns ("Nets you named"), and `--project` adds a project's chain or lines either way ("Nets of the project's chain or lines"). Each tagged net then brings the nets reached from it through two-pad series parts, and its differential partner ("Nets reached through series parts and pair partners"). Ground and power nets are never tagged. `review.json` records each net's source as `flag`, `project`, `pattern:<family>` or `walk`, the first of these that tagged it.

**f_max and L.** The basis line names the review's f_max and where it came from: `--f-max` when given; else 5 times a carrier, at most 6 GHz, the carrier being `--f0`, an antenna project's band centre or a project's f0; else a signal-integrity project's f_max, at most 6 GHz; else 5 GHz, as here. A project's own simulation f_max is never the review's. L is λ/20 in the dielectric at f_max, with the stackup's highest εr: 1.413 mm at 5 GHz and εr 4.5. R1 prints it beside a run, R2 takes the larger of L and 2 mm as its distance, and R4 holds a fence's gaps to it.

**The rules.** Each finding prints what it measured, the threshold and its source, its place in KiCad's frame (mm, y down) and the number that `review.png` and `review.csv` share. A tagged track's reference is the nearest copper layer, by dielectric distance, where a GND or power plane covers some of the centre line of its route; the net whose planes cover most of it there is its reference net, and h the dielectric between them.
- **R1** measures the runs of a tagged track's centre line that no plane of its reference net covers, on any layer, seen through cut-outs. A bare run counts from 1 mm, and a void round one via or plated hole, within its radius plus 0.6 mm, is that hole's antipad. CLK_GAP crosses a 6 × 10 mm box cut out of In1.Cu's GND with In2.Cu's +3V3 under it, so R1 fires; CLK_LOOK crosses a second box with a GND island under it on In2.Cu, so it does not.
- **R2** looks at each via where a tagged net's reference changes: between two nets, it asks for a capacitor across those two nets within d = max(L, 2 mm) of the via; between two layers of one net, for a via of that net joining them. CLK_MID changes from GND to +3V3 at a via 0.89 mm from the pads of C1, a capacitor between GND and +3V3, so R2 stays silent.
- **R3** measures how far a tagged track's edge runs from the board outline and fires under k·h, with k = 2 (`--edge-k`), printing the share of its ideal return current that would lie past the edge: CLK_EDGE runs 0.35 mm from the top edge.
- **R4** measures the gaps between the GND vias within 1 mm of each shield's frame line, along the stretches its pads cover, against L, and prints each gap in wavelengths at f_max; `--edge-fence` adds the board edge's fence. SH1's frame has a GND via every 0.976 mm here, so R4 stays silent.

**The cavities.** Two copper layers whose pours face each other, whatever their nets and less the pours of the layers between, make a plane pair, and each connected piece of 20 mm² or more is a cavity. Its first line gives the layers, the nets, a point inside it, d, the series εr through the dielectric, the area and the via posts; the next gives its modes up to f_max, solved in 2D on a 0.25 mm grid. A GND/power pair has no posts, and a pair of one net has one at each via or plated pad of that net joining the two layers. Cavity 1 is the GND/+3V3 pair; cavity 2 is In2.Cu's GND island facing In1.Cu's GND round the second box, held by the via that ties the two. A cavity with no post also has a static mode at 0 Hz, its two planes charged against each other as one capacitor: that is no resonance, so no line or table lists it, and `review.json` keeps it as the cavity's first mode, at 0 Hz. A mode is marked when it lies within ±5 % of a harmonic of the carrier, its fundamental included, or of a clock that `--clock` names (repeatable), a window that covers εr's tolerance, the missing fringing and the solver. A clock's marks stop after its 10th harmonic, where its harmonics lie closer than twice the window, and a line says so when f_max reaches its 11th; the carrier's never stop. A cavity solved on a coarser grid, or holding a slot under 0.5 mm, gets a warning line.

**`review`** on `lpf915`, whose RF nets match no pattern, so `--net` names them, with its 915 MHz carrier:

```
<venv>\Scripts\kicad-rf-studio review tests/fixtures/lpf915.kicad_pcb --net "RF_*" --f0 915MHz -o review
```

It took 1.5 s and replaced the first review's files. Its basis line gives f_max 4.575 GHz, 5 times the carrier, and λ/20 1.545 mm, and its tags line the five nets that `RF_*` matched. This excerpt keeps the R4 finding, the cavity lines and the limits:

```
#1 R4: the via fence (SH1) leaves 47.200 mm of its line with no GND via, 1.53 λ at f_max, at (117.325, 89.250) mm, over λ/20 = 1.545 mm (Bahl; Harper; Archambeault).
Cavity 1: F.Cu/B.Cu, nets GND / GND, at (118.782, 100.255) mm: d 0.710 mm, εr 4.5, area 582.7 mm², via posts 36.
Cavity 1's modes up to f_max, in MHz: 2430.8, 2948.4, 3570.7, 3926.4.
Cavity 1's mode at 3570.7 MHz lies within ±5 % of 4 × the carrier, 915 MHz.
Limits of the cavity modes: lossless, so the list says where a resonance may sit, never how high it rises; decoupling capacitors excluded; vias as posts only, snapped to the grid, and a post of drill 0.5 mm or more, a disc of held cells, puts the mode it makes up to about 6 % low; TM0 modes only; no fringing, so frequencies read high by about 2Δ/a, Δ about 0.4 to 0.5 d (about 0.3 % for d 0.2 mm on 50 mm, 2 % for 1 mm; gate E-E's openEMS run measured 1.0 % on a 50 × 30 mm pair at d 0.8 mm); εr uniform; the fills as saved; slots under 0.5 mm unresolved; cavities uncoupled across splits.
Limit: board-level keep-out areas leave no geometry in the import, so the review sees only the fills they shape; a footprint's keep-out, a connector or a printed antenna takes its copper out of R1 and R3.
```

SH1, the shield over the filter, has no GND via within 1 mm of its frame line, so the whole 47.2 mm that its pads cover is one gap. The board's two GND pours, on F.Cu and B.Cu, face each other over 582.7 mm², held by 36 vias, and the mode at 3570.7 MHz lies 2.4 % under the carrier's 4th harmonic, 3660 MHz.

In the GUI, the Review tab, after Project, takes the board, the Tagged nets (names or patterns, comma-separated; empty for the name patterns) and the f0, as `--net` and `--f0`; Review the board runs the review with the open project, if any, as `--project`. It lists the review's lines, the findings by number, rule, net, layer and place, and the cavity modes with the harmonic each lies near, beside `review.png`. It writes into the per-user data folder's `review` folder, replaced on each review, and never into your KiCad project. Select in KiCad selects the items of the findings picked in the table in KiCad's PCB editor. It needs a press of the kicad-rf-studio button in KiCad first, since it talks only to the KiCad that pressed it, and stays off until then; it refuses when KiCad has another board open, and it never zooms. When KiCad selects fewer items than it was sent, the board open there holds edits not yet saved: save it, then press Review the board again. A press while the Review tab is shown keeps it shown and fills its board. Simulate this, on one R1, R2 or R3 finding, pre-fills New with the kind Signal integrity on that finding's net and switches to Project, whose status line says that the run gives one relative result and that a comparison needs a twin board drawn in KiCad, with the copper fixed or the trace moved, and a project of each; for an R3 finding, also that signal integrity measures the line, not the radiation from the board edge.

### What these results do not tell you

- Every review carries this line: "Geometry rules, not a compliance verdict: each finding measures the board as saved against a published rule of thumb, named with its source; nothing here predicts a pass or a fail."
- Each threshold comes from the source its finding names: LearnEMC, Ansys SIwave and HyperLynx DRC for R1, TI SLLA656 and Siemens for R2, LearnEMC for R3's 2h, and λ/20 after Bahl, Harper and Archambeault for R4. Their numbers, f_max 5 GHz, R1's 1 mm run, R2's max(L, 2 mm), k = 2, the cavity marks' ±5 % window and the tag patterns with their deny words, were set on three public boards only, by one judge: R1 found 5 true positives in 8 there (62 %) when it looked through to any net's plane, and its same-net form has not been measured since. Running the review on your own boards is what calibrates them.
- R2 is for information: no source derives its distance, and those boards gave it no true positive to calibrate against.
- R4 prints a gap against λ/20, never an attenuation. By a wire-grid estimate, a single row of vias lets through about −20 dB at a λ/20 pitch and about −10 dB at λ/10; no finding prints that figure.
- The review ends with this line: "Limit: board-level keep-out areas leave no geometry in the import, so the review sees only the fills they shape; a footprint's keep-out, a connector or a printed antenna takes its copper out of R1 and R3."
- Every cavity list ends with its limits: "Limits of the cavity modes: lossless, so the list says where a resonance may sit, never how high it rises; decoupling capacitors excluded; vias as posts only, snapped to the grid, and a post of drill 0.5 mm or more, a disc of held cells, puts the mode it makes up to about 6 % low; TM0 modes only; no fringing, so frequencies read high by about 2Δ/a, Δ about 0.4 to 0.5 d (about 0.3 % for d 0.2 mm on 50 mm, 2 % for 1 mm; gate E-E's openEMS run measured 1.0 % on a 50 × 30 mm pair at d 0.8 mm); εr uniform; the fills as saved; slots under 0.5 mm unresolved; cavities uncoupled across splits."

## Development setup

1. Create a virtual environment: `python -m venv .venv`
2. Activate it: `.venv\Scripts\activate` on Windows, `source .venv/bin/activate` elsewhere.
3. Install the package in editable mode with the development extras: `python -m pip install -e .[dev]`
4. Give the venv openEMS as Install says (on Windows, `kicad-rf-studio setup-openems <openEMS folder>`, and `CSXCAD_INSTALL_PATH` set to that folder: the tests import openEMS in this Python, which reads it to find openEMS's DLLs). Without it, the tests marked `openems` are skipped.
5. Run the tests: `python -m pytest -q`
6. Before a release, run `python tools/release_check.py`: it builds a wheel from git archive of HEAD and checks it, installs it in a fresh venv, starts the GUI there offscreen, runs `new --antenna` there on `tests/fixtures/ifa2g4_pi.kicad_pcb`, `new --interface` on `tests/fixtures/usb2_hs.kicad_pcb` and `review` on `tests/fixtures/emc_review.kicad_pcb`, whose `review.json` it compares with the committed golden, checks the KiCad button's plugin.json against KiCad's schemas, and runs the privacy gate's generic rules over the history and the wheel. One real run through the GUI, lpf915 at Draft then its verify, runs with `KRS_E2E_DIR` set to an empty folder outside the repository and openEMS importable (step 4): `python -X utf8 -m pytest tests/test_gui.py -k real_run -s`. It takes about lpf915's Draft run plus its verify, and its cost line prints the estimate first; a file named STOP in its newest run folder stops it. One antenna project through the GUI, `ifa2g4_pi` at Normal run, retuned, verified and compared with a verified ground-pour project, runs with `KRS_E2E_DIR` set to an empty folder outside the repository and `KRS_E2E_VARIANT` to that project's `project.json`, or to `window` to make the pour through the GUI first: `python -X utf8 -m pytest tests/test_gui.py -k antenna_project_through -s`. It takes about the pi project's run plus its verify, 1.4 h on the development PC (about 2.9 h with `window`, which also runs and verifies the pour). One signal-integrity project through the GUI, `usb2_hs` at Normal run, retuned, verified and compared with a verified plane-gap project, runs with `KRS_E2E_DIR` set to an empty folder outside the repository and `KRS_E2E_SI_VARIANT` to that project's `project.json`: `python -X utf8 -m pytest tests/test_gui.py -k si_project_through -s`. It takes about usb2_hs's run plus its verify, 1.2 h on the development PC, after the variant's own run, retune and verify by the command line.
7. After a change to a message in `src/kicad_rf_studio/core/messages.py`, run `python tools/catalog.py` (Babel comes with the dev extras), translate each entry of `po/pt_BR.po` whose msgstr is empty (a changed message's old translation stays at the file's end as a `#~` entry), then run it again: the tests refuse a catalog that is not complete and compiled. They run in English whatever your system's language, and `KRS_TEST_LANGUAGE=pt_BR` runs `tests/test_gui.py` in Brazilian Portuguese.

## Contributing

Set up the local privacy gate before you commit or push. It refuses private names, absolute drive and home paths, network shares and e-mail addresses. CI repeats only the generic checks.

1. Write the words that must never leave your machine in a UTF-8 text file kept outside the repository, one per line. Blank lines and lines starting with `#` are ignored, and matching ignores case.
2. Point `KRS_PRIVATE_LIST` at that file. In PowerShell: `$env:KRS_PRIVATE_LIST = "<path to the file>"`. In a POSIX shell: `export KRS_PRIVATE_LIST=<path to the file>`.
3. Enable the hooks: `git config core.hooksPath .githooks`

The hooks run `tools/privacy_gate.py` with the Python found on your `PATH`; it needs only the standard library. Without a usable list they refuse the commit or push. `python tools/privacy_gate.py --all` scans the whole history by hand.

A hit prints as `<where>:<line>: <rule>`. `deny#N` is the N-th entry of your list, counting entries only, and `generic:...` is one of the built-in rules. The gate never prints matched text; a file whose name matched shows as `path#N`.

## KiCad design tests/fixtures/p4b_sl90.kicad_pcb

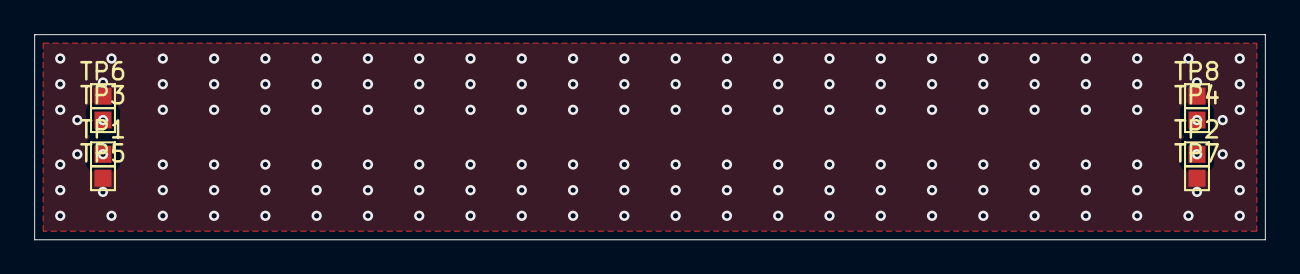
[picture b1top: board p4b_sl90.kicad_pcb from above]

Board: 4 copper layers, 72.0 x 12.0 mm, 8 parts (0 on the bottom side), 3 nets.

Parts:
TP1, TP2, TP3, TP4, TP5, TP6, TP7, TP8: TP; TestPoint_Pad_1.0x1.0mm

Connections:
D+: TP1.1, TP2.1
D-: TP3.1, TP4.1
GND: TP5.1, TP6.1, TP7.1, TP8.1
